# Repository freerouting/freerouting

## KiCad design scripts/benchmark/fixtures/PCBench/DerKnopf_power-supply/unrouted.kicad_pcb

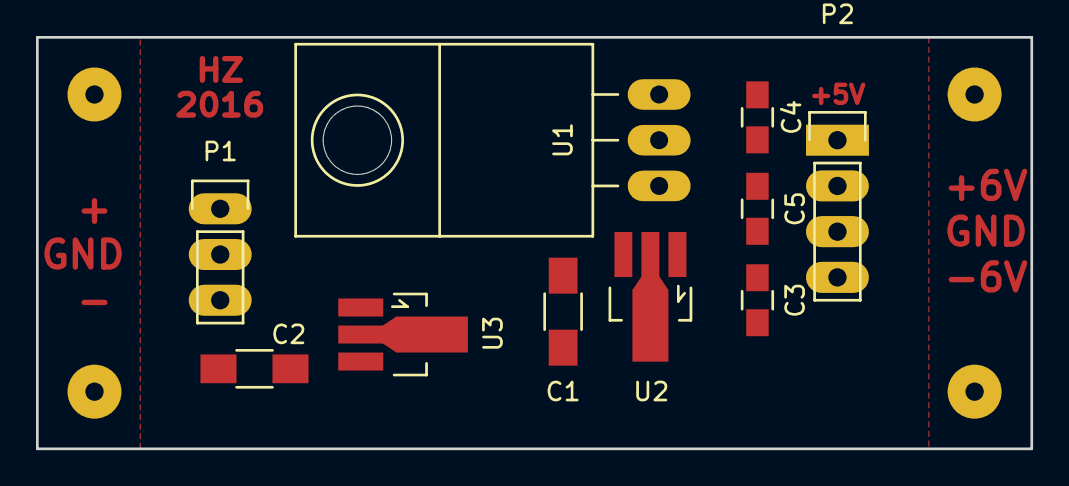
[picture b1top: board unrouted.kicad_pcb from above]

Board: 2 copper layers, 55.2 x 22.9 mm, 14 parts (0 on the bottom side), 6 nets, no tracks yet.

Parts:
C1, C2: 10u; C_1206_HandSoldering
C3, C4, C5: 100n; C_0805_HandSoldering
P1: CONN_01X03; Pin_Header_Straight_1x03
P2: CONN_01X04; Pin_Header_Straight_1x04
R: D; Pin_Header_Straight_1x01
R_2, R_3, R_4: D; Pin_Header_Straight_1x01
U1: 7805; TO-220_Neutral123_Horizontal_LargePads
U2: 78L06; SOT89-3_Housing_Handsoldering
U3: 79L06; SOT89-3_Housing_Handsoldering

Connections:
/+5V: C4.1, P2.1, U1.3
/+6V: C5.1, P2.2, U2.1
/+15V: C1.1, P1.1, U1.1, U2.3
/-6V: C3.1, P2.4, U3.3
/-15V: C2.1, P1.3, U3.2
GND: C1.2, C2.2, C3.2, C4.2, C5.2, P1.2, P2.3, U1.2, U2.2, U3.1

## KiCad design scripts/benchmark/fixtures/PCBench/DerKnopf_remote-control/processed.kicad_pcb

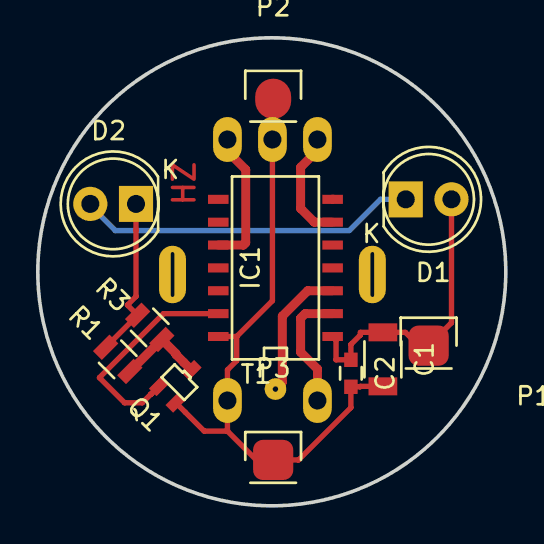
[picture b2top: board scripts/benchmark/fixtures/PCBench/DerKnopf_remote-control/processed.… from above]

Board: 2 copper layers, 26.0 x 26.0 mm, 13 parts (1 on the bottom side), 10 nets.

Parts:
C1: 22u; C_1206
C2: 100n; C_0603
D1, D2: LED; LED-5MM
E1: Encoder; MechanicalEncoder
IC1: ATTINY44-S; SOIC-14_N
P1: Bat+; Pin_Header_Straight_1x01
P2, P3: Bat-; Pin_Header_Straight_1x01
Q1: MTM232270; SOT-323
R1, R3: 4R7; R_0805
T1: TEST; TestPoint

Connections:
/A: E1.1, IC1.6
/B: E1.3, IC1.10
/Button: E1.4, IC1.2
/IROUT: IC1.13, Q1.1
/LED-connect: D1.1, D2.2
/LEDPower: D2.1, R1.1, R3.1
GND: C1.2, C2.2, E1.2, E1.5, IC1.14, P2.1, P3.1, Q1.2
unnamed: IC1.3, T1.1
unnamed: Q1.3, R1.2, R3.2
VCC: C1.1, C2.1, D1.2, IC1.1, P1.1

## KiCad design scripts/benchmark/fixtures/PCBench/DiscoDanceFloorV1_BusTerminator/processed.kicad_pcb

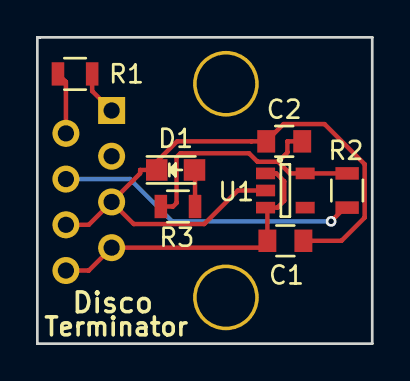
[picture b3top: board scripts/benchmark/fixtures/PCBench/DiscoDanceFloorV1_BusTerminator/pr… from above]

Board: 2 copper layers, 18.6 x 17.0 mm, 8 parts (1 on the bottom side), 7 nets.

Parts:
C1: 1.0uF; C_0805
C2: 2.2uF; C_0805
D1: LED; LED_0805
J1: RJ45; RJ45_8
R1: 120; R_0805
R2: 20k; R_0805
R3: 200; R_0805
U1: AP2204K-5.0TRG1; SOT-23-5

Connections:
+5V: C2.1, R2.1, R3.1, U1.5
GND: C1.2, C2.2, D1.1, J1.5, J1.6, U1.2
unnamed: D1.2, R3.2
unnamed: J1.1, R1.2
unnamed: J1.2, R1.1
unnamed: J1.4, R2.2
VCC: C1.1, J1.7, J1.8, U1.1, U1.3

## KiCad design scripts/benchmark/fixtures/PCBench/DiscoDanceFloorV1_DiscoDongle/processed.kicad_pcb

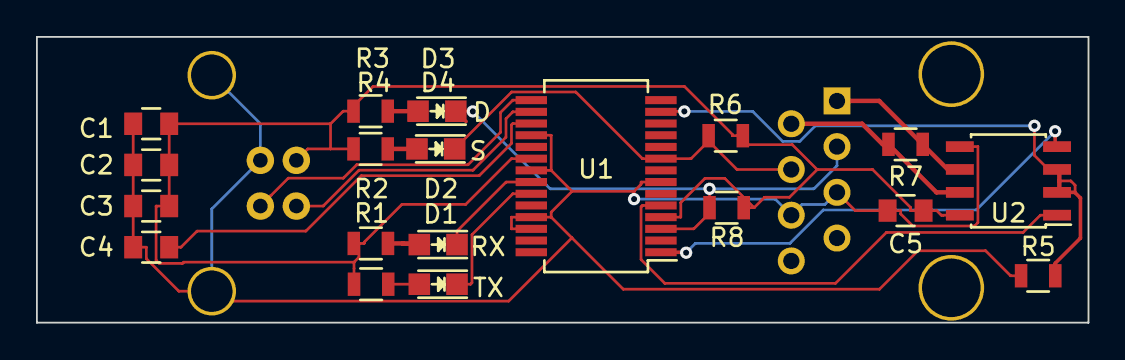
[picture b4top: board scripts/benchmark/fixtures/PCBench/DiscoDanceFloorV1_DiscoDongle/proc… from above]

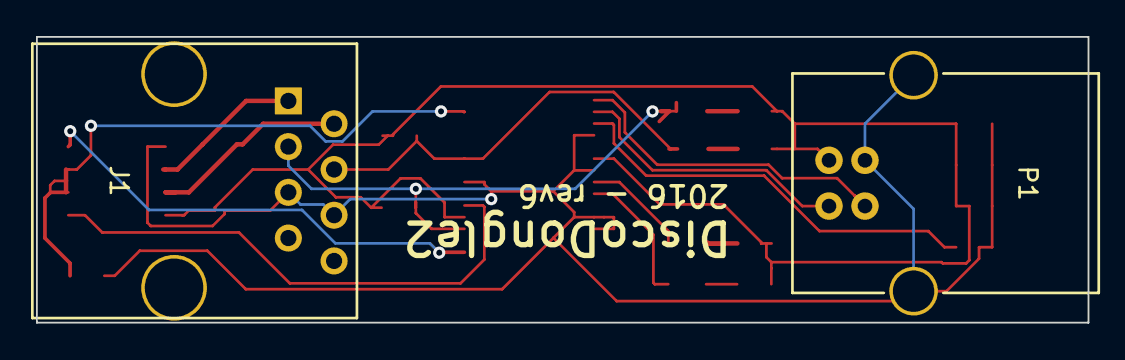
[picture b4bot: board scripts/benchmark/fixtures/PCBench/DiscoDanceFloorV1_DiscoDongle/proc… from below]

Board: 2 copper layers, 58.4 x 15.9 mm, 21 parts (2 on the bottom side), 18 nets.

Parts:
C1, C4, C5: 100nF; C_0805
C2: 4.7uF; C_0805
C3: 10nF; C_0805
D1: TX; LED_0805
D2: RX; LED_0805
D3: D; LED_0805
D4: S; LED_0805
J1: RJ45; RJ45_8
P1: USB_B
R1, R2, R3, R4: 200; R_0805
R5, R6, R8: 20k; R_0805
R7: 120; R_0805
U1: FT232RL; SSOP-28_5.3x10.2mm_Pitch0.65mm
U2: ISL81487E; SOIC-8_3.9x4.9mm_Pitch1.27mm

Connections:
+5V: C1.1, C2.1, C3.1, C5.1, P1.1, R1.1, R2.1, R3.1, R4.1, R6.1, R8.1, U1.4, U1.20, U2.8
Daisy: D3.1, J1.3, R8.2, U1.3
GND: C1.2, C2.2, C3.2, C4.2, C5.2, J1.5, J1.6, P1.4, P1.5, R5.2, U1.7, U1.18, U1.21, U1.25, U1.26, U2.5
unnamed: C4.1, U1.17
unnamed: D1.2, R1.2
unnamed: D2.2, R2.2
unnamed: D3.2, R3.2
unnamed: D4.2, R4.2
unnamed: J1.1, R7.2, U2.6
unnamed: J1.2, R7.1, U2.7
unnamed: P1.2, U1.16
unnamed: P1.3, U1.15
unnamed: R5.1, U1.13, U2.2, U2.3
unnamed: U1.1, U2.4
unnamed: U1.5, U2.1
RXLED: D2.1, U1.22
Signal: D4.1, J1.4, R6.2, U1.9
TXLED: D1.1, U1.23
